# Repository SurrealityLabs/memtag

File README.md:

# sharptag
A CircuitPython display using a Sharp Memory LCD

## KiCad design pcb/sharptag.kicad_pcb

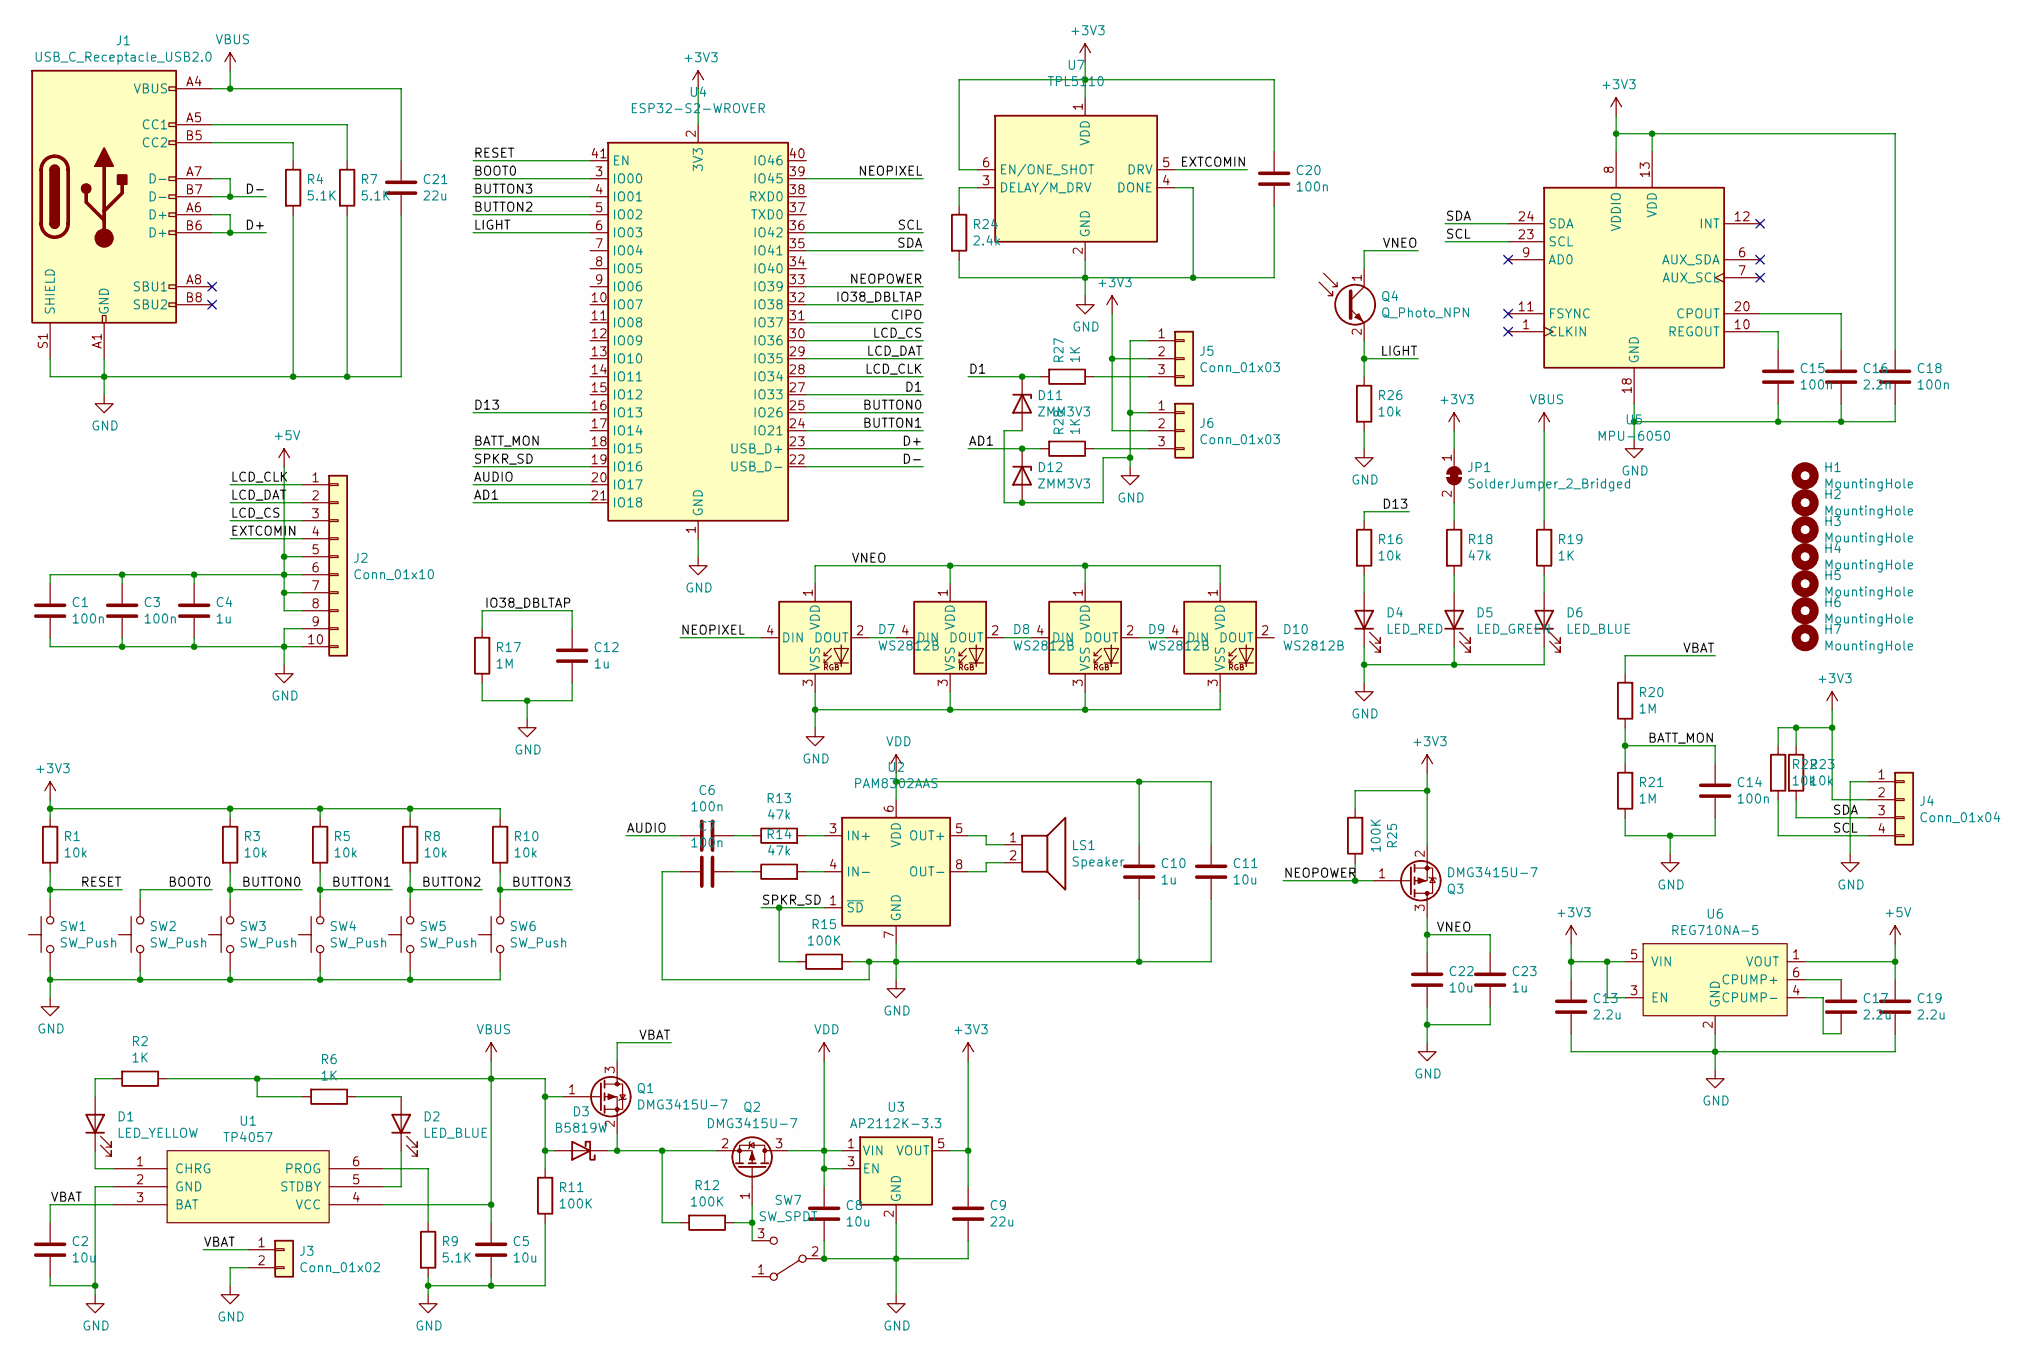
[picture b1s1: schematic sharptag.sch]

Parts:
C1, C3, C6, C7, C14, C15, C18, C20: 100n; C_0603_1608Metric; LCSC C14663
C2, C5, C8, C11, C22: 10u; C_0805_2012Metric; LCSC C15850
C4, C10, C12, C23: 1u; C_0603_1608Metric; LCSC C15849
C9, C21: 22u; C_0805_2012Metric; LCSC C45783
C13, C19: 2.2u; C_1206_3216Metric; LCSC C50254
C16: 2.2n; C_0603_1608Metric; LCSC C1604
C17: 2.2u; C_0805_2012Metric; LCSC C5378
D1: LED_YELLOW; LED_0603_1608Metric; LCSC C72038
D2, D6: LED_BLUE; LED_0603_1608Metric; LCSC C72041
D3: B5819W; D_SOD-123; LCSC C8598
D4: LED_RED; LED_0603_1608Metric; LCSC C2286
D5: LED_GREEN; LED_0603_1608Metric; LCSC C72043
D7, D8, D9, D10: WS2812B; LED_WS2812B_PLCC4_5.0x5.0mm_P3.2mm
D11, D12: ZMM3V3; D_MiniMELF; LCSC C8056
H1, H2, H3, H4: MountingHole; MountingHole_3.2mm_M3_DIN965
H5, H6, H7: MountingHole; tooling-hole
J1: USB_C_Receptacle_USB2.0; USB_C_Receptacle_HRO_TYPE-C-31-M-12; LCSC C165948
J2: Conn_01x10; TE_1-1734839-0_1x10-1MP_P0.5mm_Horizontal
J3: Conn_01x02; JST_PH_S2B-PH-SM4-TB_1x02-1MP_P2.00mm_Horizontal
J4: Conn_01x04; JST_SH_SM04B-SRSS-TB_1x04-1MP_P1.00mm_Horizontal
J5, J6: Conn_01x03; JST_PH_S3B-PH-SM4-TB_1x03-1MP_P2.00mm_Horizontal
JP1: SolderJumper_2_Bridged; SolderJumper-2_P1.3mm_Bridged2Bar_RoundedPad1.0x1.5mm
LS1: Speaker; MagneticBuzzer_Kobitone_254-EMB84Q-RO; LCSC C94599
Q1, Q2, Q3: DMG3415U-7; SOT-23; LCSC C96616
Q4: Q_Photo_NPN; D_0603_1608Metric; LCSC C146233
R1, R3, R5, R8, R10, R16, R22, R23, R26: 10k; R_0603_1608Metric; LCSC C25804
R2, R6, R19, R27, R28: 1K; R_0603_1608Metric; LCSC C21190
R4, R7, R9: 5.1K; R_0603_1608Metric; LCSC C23186
R11, R12, R15, R25: 100K; R_0603_1608Metric; LCSC C25803
R13, R14, R18: 47k; R_0603_1608Metric; LCSC C25819
R17, R20, R21: 1M; R_0603_1608Metric; LCSC C22935
R24: 2.4k; R_0603_1608Metric; LCSC C22940
SW1, SW2, SW3, SW4, SW5, SW6: SW_Push; SW_SPST_CK_RS282G05A3; LCSC C412368
SW7: SW_SPDT; SW_SPDT_PCM12; LCSC C431541
U1: TP4057_[C12044]; SOT-23-6
U2: PAM8302AAS; MSOP-8_3x3mm_P0.65mm; LCSC C113367
U3: AP2112K-3.3; SOT-23-5; LCSC C51118
U4: ESP32-S2-WROVER
U5: MPU-6050; InvenSense_QFN-24_4x4mm_P0.5mm; LCSC C24112
U6: REG710NA-5; SOT-23-6; LCSC C179084
U7: TPL5110; SOT-23-6; LCSC C125830

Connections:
+3V3: C9.1, C13.1, C18.1, C20.1, J4.2, J5.2, J6.2, JP1.1 (A), Q3.2 (S), R1.1, R3.1, R5.1, R8.1, R10.1, R22.1, R23.1, R25.2, U3.5 (VOUT), U4.2 (3V3), U5.8 (VDDIO), U5.13 (VDD), U6.3 (EN), U6.5 (VIN), U7.1 (VDD), U7.6 (EN/ONE_SHOT)
+5V: C1.1, C3.1, C4.1, C19.1, J2.5, J2.6, J2.7, J2.8, U6.1 (VOUT)
/AD1: D12.1 (K), R28.2, U4.21 (IO18)
/AUDIO: C6.1, U4.20 (IO17)
/BATT_MON: C14.1, R20.1, R21.2, U4.18 (IO15)
/BOOT0: SW2.2, U4.3 (IO00)
/BUTTON0: R3.2, SW3.2, U4.25 (IO26)
/BUTTON1: R5.2, SW4.2, U4.24 (IO21)
/BUTTON2: R8.2, SW5.2, U4.5 (IO02)
/BUTTON3: R10.2, SW6.2, U4.4 (IO01)
/CIPO: U4.31 (IO37)
/D1: D11.1 (K), R27.2, U4.27 (IO33)
/D13: R16.1, U4.16 (IO13)
/D+: J1.A6 (D+), J1.B6 (D+), U4.23 (USB_D+)
/D-: J1.A7 (D-), J1.B7 (D-), U4.22 (USB_D-)
/EXTCOMIN: J2.4, U7.5 (DRV)
/IO38_DBLTAP: C12.1, R17.2, U4.32 (IO38)
/LCD_CLK: J2.1, U4.28 (IO34)
/LCD_CS: J2.3, U4.30 (IO36)
/LCD_DAT: J2.2, U4.29 (IO35)
/LIGHT: Q4.2 (E), R26.1, U4.6 (IO03)
/NEOPIXEL: D7.4 (DIN), U4.39 (IO45)
/NEOPOWER: Q3.1 (G), R25.1, U4.33 (IO39)
/RESET: R1.2, SW1.2, U4.41 (EN)
/SCL: J4.4, R22.2, U4.36 (IO42), U5.23 (SCL)
/SDA: J4.3, R23.2, U4.35 (IO41), U5.24 (SDA)
/SPKR_SD: R15.1, U2.1 (~SD), U4.19 (IO16)
/VBAT: C2.1, J3.1, Q1.3 (D), R20.2, U1.3 (BAT)
/VNEO: C22.1, C23.1, D7.1 (VDD), D8.1 (VDD), D9.1 (VDD), D10.1 (VDD), Q3.3 (D), Q4.1 (C)
GND: C1.2, C2.2, C3.2, C4.2, C5.2, C7.2, C8.2, C9.2, C10.2, C11.2, C12.2, C13.2, C14.2, C15.2, C16.2, C18.2, C19.2, C20.2, C21.2, C22.2, C23.2, D4.1 (K), D5.1 (K), D6.1 (K), D7.3 (VSS), D8.3 (VSS), D9.3 (VSS), D10.3 (VSS), D11.2 (A), D12.2 (A), J1.A1 (GND), J1.A12 (GND), J1.B1 (GND), J1.B12 (GND), J1.S1 (SHIELD), J2.9, J2.10, J3.2, J4.1, J5.1, J6.1, R4.2, R7.2, R9.2, R11.1, R15.2, R17.1, R21.1, R24.2, R26.2, SW1.1, SW2.1, SW3.1, SW4.1, SW5.1, SW6.1, SW7.2 (B), U1.2 (GND), U2.7 (GND), U3.2 (GND), U4.1 (GND), U4.26 (GND), U4.42 (GND), U4.43 (GND), U5.18 (GND), U6.2 (GND), U7.2 (GND), U7.4 (DONE)
unnamed: C6.2, R13.1
unnamed: C7.1, R14.1
unnamed: C15.1, U5.10 (REGOUT)
unnamed: C16.1, U5.20 (CPOUT)
unnamed: C17.1, U6.6 (CPUMP+)
unnamed: C17.2, U6.4 (CPUMP-)
unnamed: D1.1 (K), U1.1 (CHRG)
unnamed: D1.2 (A), R2.2
unnamed: D2.1 (K), U1.5 (STDBY)
unnamed: D2.2 (A), R6.1
unnamed: D3.1 (K), Q1.2 (S), Q2.2 (S), R12.2
unnamed: D4.2 (A), R16.2
unnamed: D5.2 (A), R18.2
unnamed: D6.2 (A), R19.1
unnamed: D7.2 (DOUT), D8.4 (DIN)
unnamed: D8.2 (DOUT), D9.4 (DIN)
unnamed: D9.2 (DOUT), D10.4 (DIN)
unnamed: J1.A5 (CC1), R7.1
unnamed: J1.B5 (CC2), R4.1
unnamed: J5.3, R27.1
unnamed: J6.3, R28.1
unnamed: JP1.2 (B), R18.1
unnamed: LS1.1, U2.5 (OUT+)
unnamed: LS1.2, U2.8 (OUT-)
unnamed: Q2.1 (G), R12.1, SW7.3 (C)
unnamed: R9.1, U1.6 (PROG)
unnamed: R13.2, U2.3 (IN+)
unnamed: R14.2, U2.4 (IN-)
unnamed: R24.1, U7.3 (DELAY/M_DRV)
VBUS: C5.1, C21.1, D3.2 (A), J1.A4 (VBUS), J1.A9 (VBUS), J1.B4 (VBUS), J1.B9 (VBUS), Q1.1 (G), R2.1, R6.2, R11.2, R19.2, U1.4 (VCC)
VDD: C8.1, C10.1, C11.1, Q2.3 (D), U2.6 (VDD), U3.1 (VIN), U3.3 (EN)

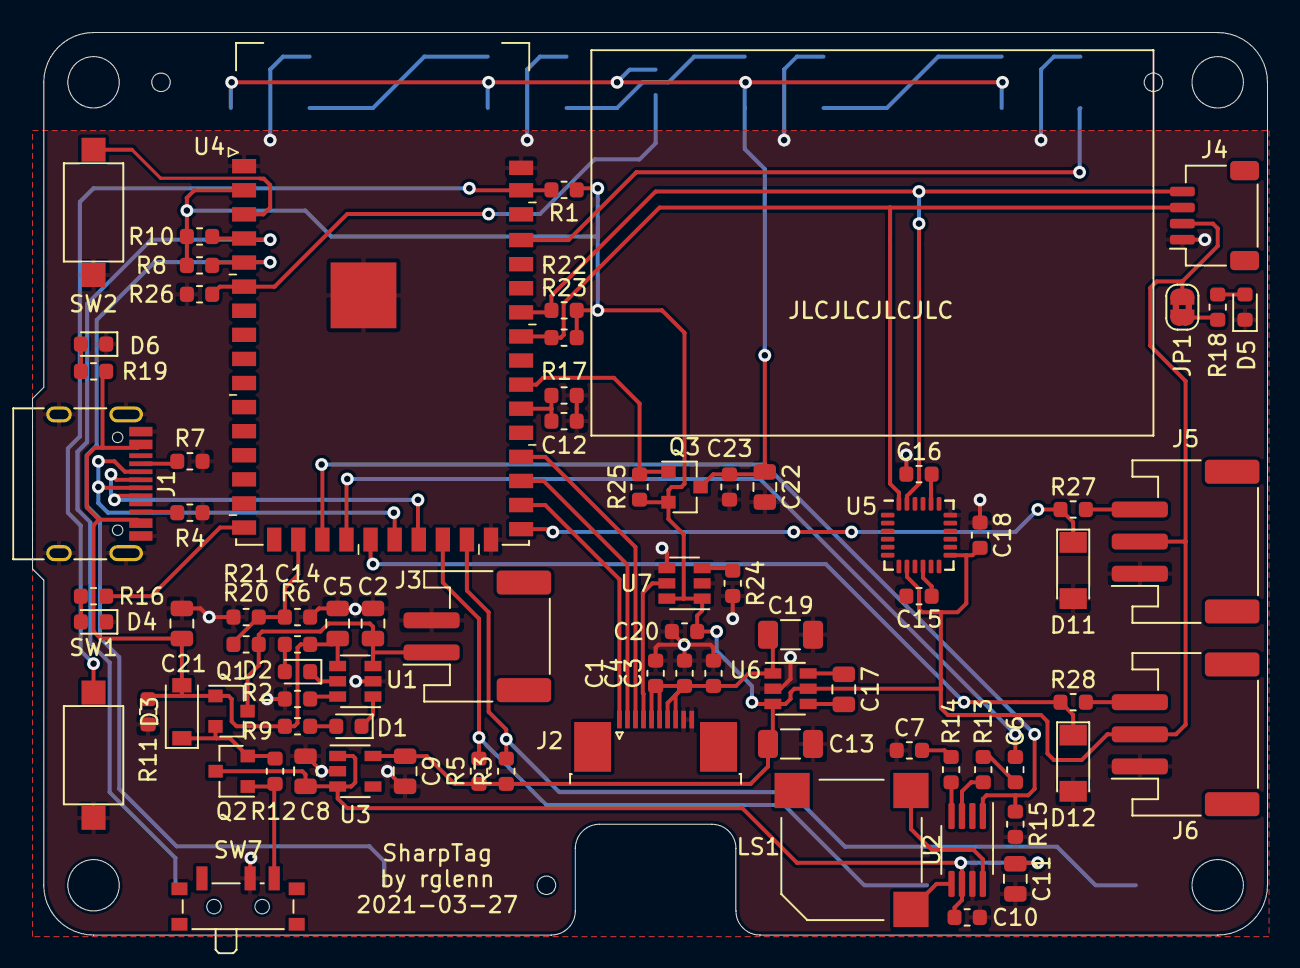
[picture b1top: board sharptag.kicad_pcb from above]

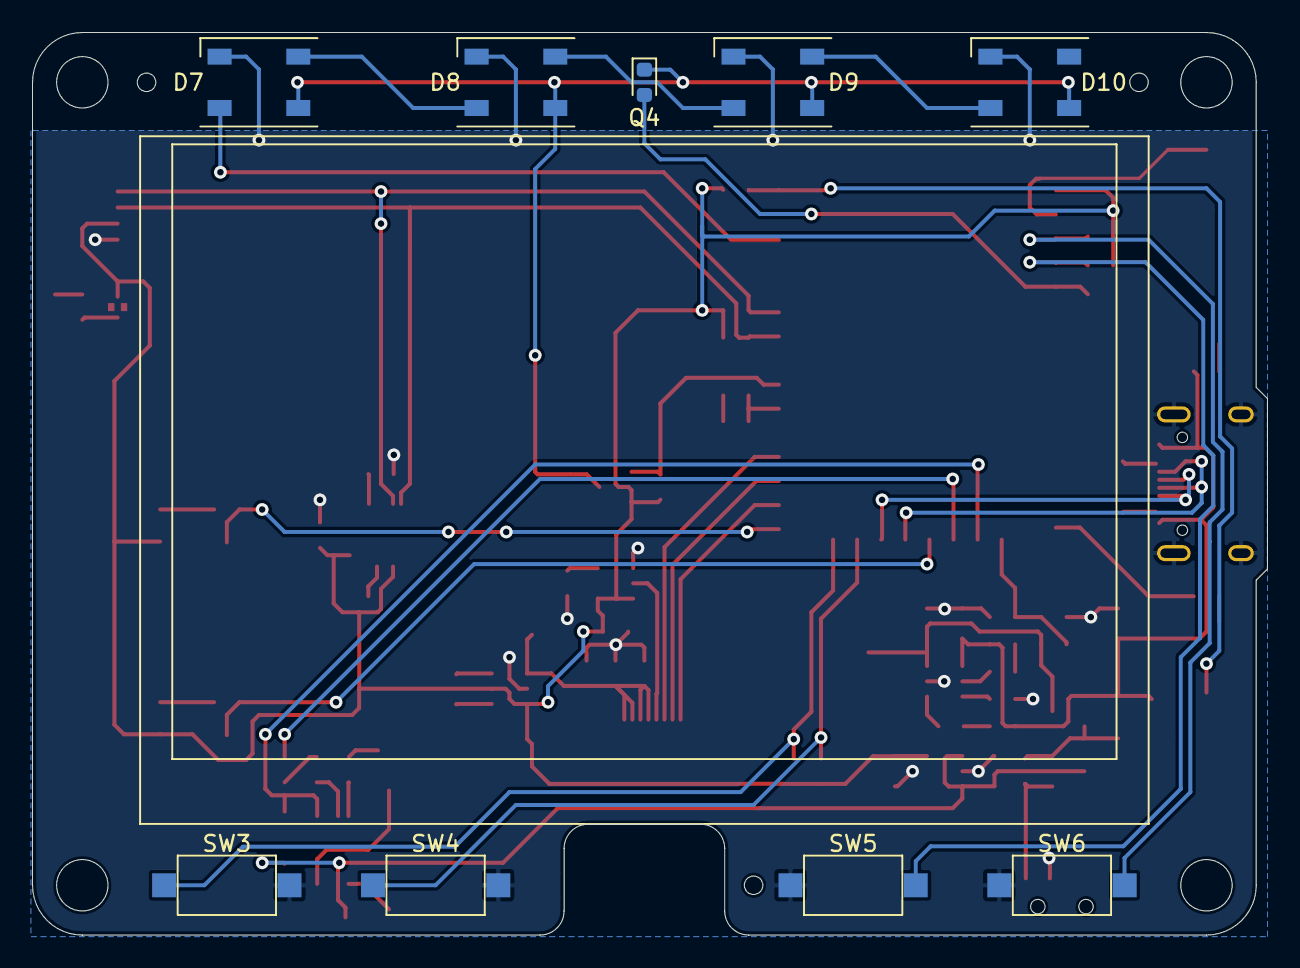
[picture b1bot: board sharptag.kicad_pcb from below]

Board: 2 copper layers, 76.9 x 56.2 mm, 96 parts (9 on the bottom side), 60 nets.

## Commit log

2021-03-21 Adding existing PCB work
2021-03-27 Layout almost complete. Needs tooling holes.
2021-03-27 Added tooling holes.
2021-03-28 Adding manufacturing data
